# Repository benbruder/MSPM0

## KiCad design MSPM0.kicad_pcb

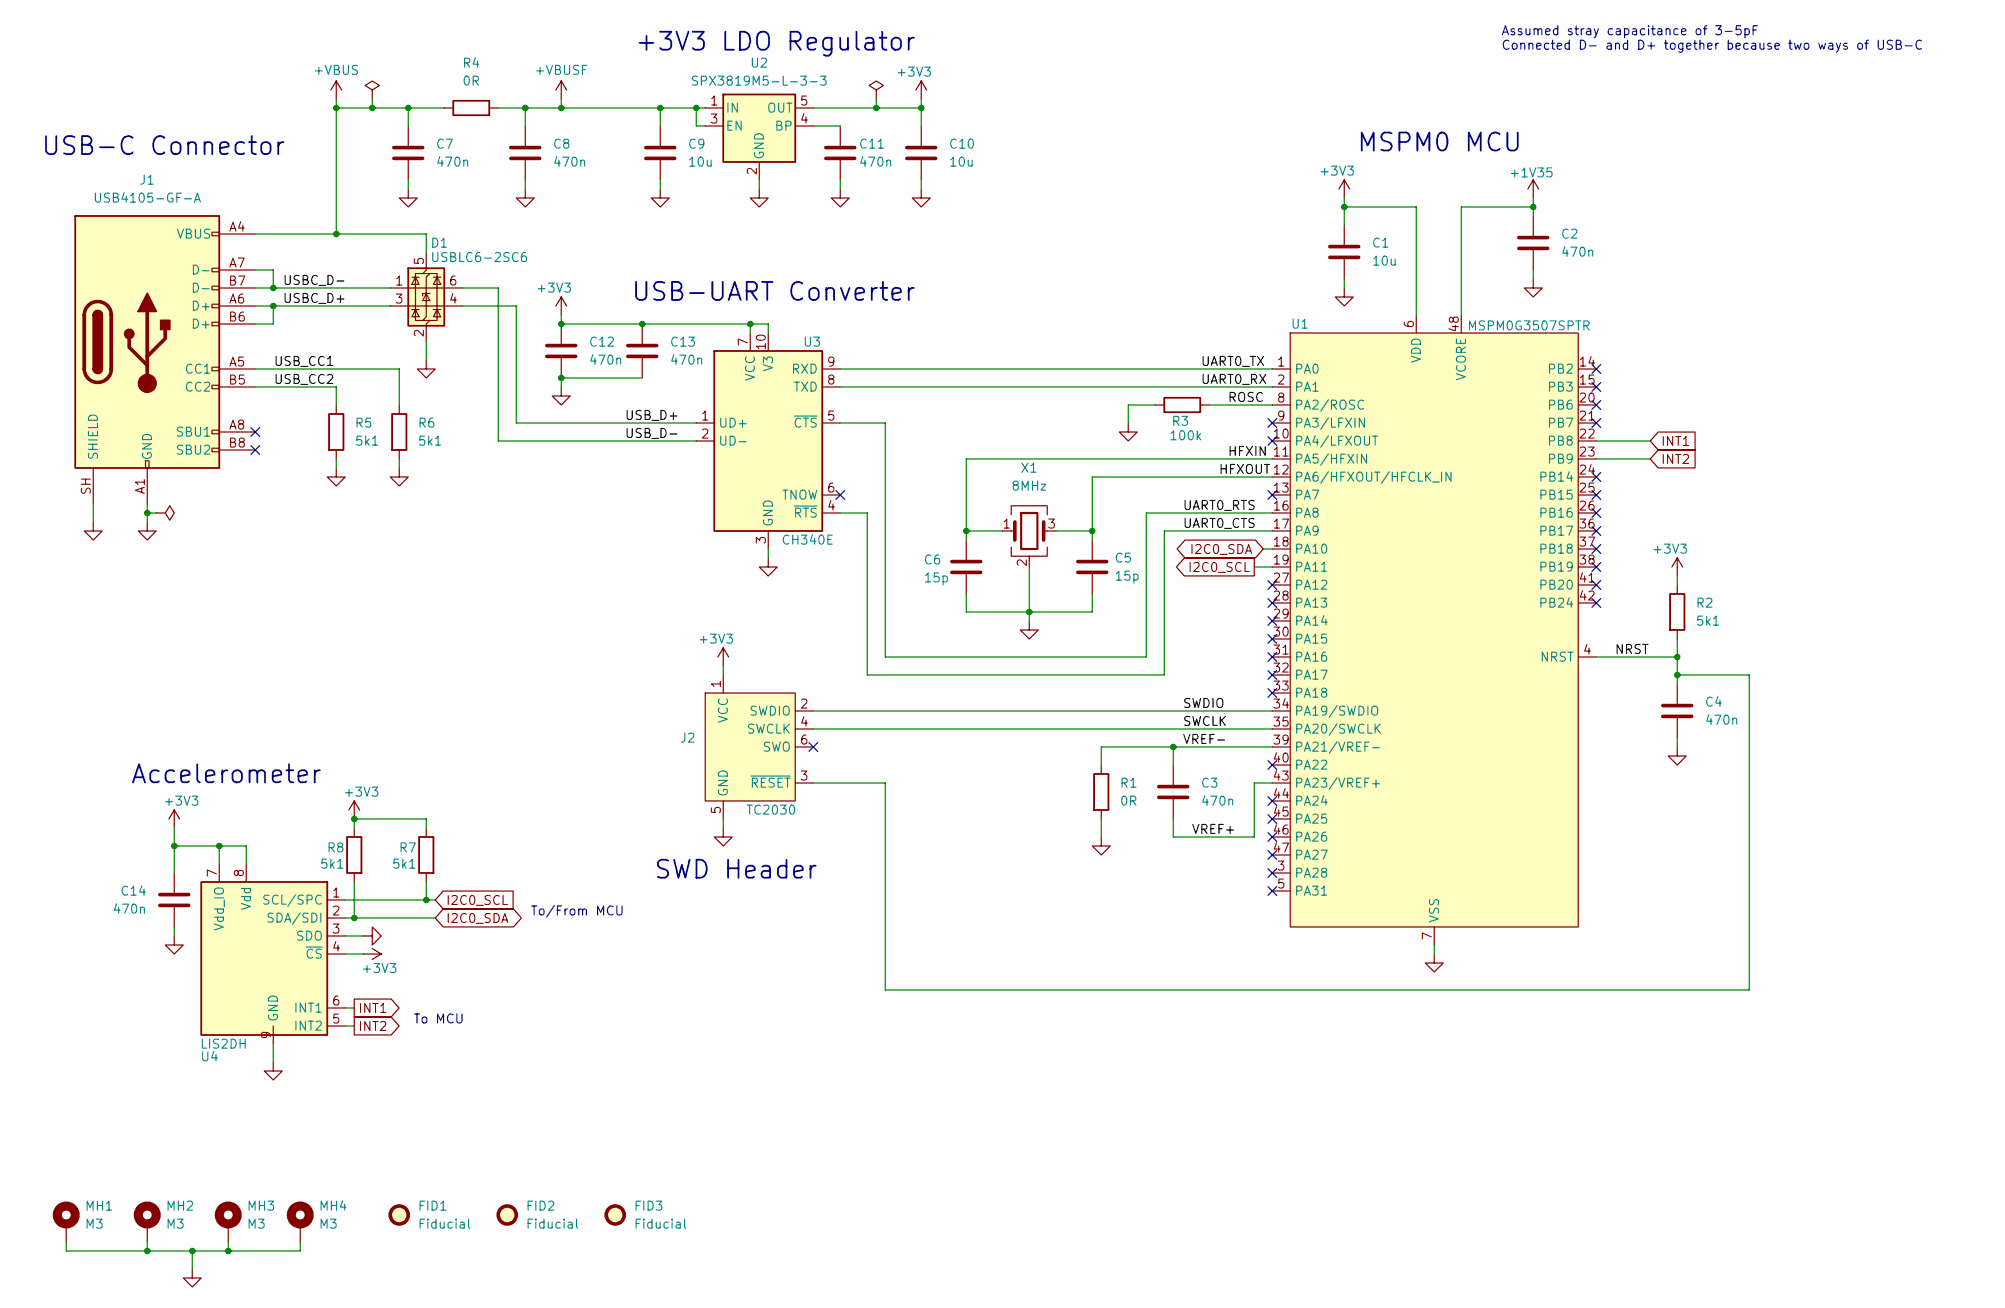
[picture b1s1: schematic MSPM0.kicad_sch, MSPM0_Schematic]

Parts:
C1, C9, C10: 10u; C_0805_2012Metric; Manufacturer Part No. CL21A106KAYNNNE; LCSC C15850
C2, C3, C4, C7, C8, C11, C12, C13, C14: 470n; C_0603_1608Metric; Manufacturer Part No. CL10B474KA8NNNC; LCSC C1623
C5, C6: 15p; C_0603_1608Metric; Manufacturer Part No. CL10C150JB8NNNC
D1: USBLC6-2SC6; SOT-23-6
FID1, FID2, FID3: Fiducial; Fiducial_1mm_Mask2mm
J1: USB4105-GF-A; USB_C_Receptacle_GCT_USB4105-xx-A_16P_TopMnt_Horizontal
J2: TC2030; Tag-Connect_TC2030-IDC-FP_2x03_P1.27mm_Vertical
MH1, MH2, MH3, MH4: M3; MountingHole_3.2mm_M3_Pad_Via
R1, R4: 0R; C_0603_1608Metric
R2, R5, R6, R7, R8: 5k1; C_0603_1608Metric
R3: 100k; C_0603_1608Metric; Manufacturer Part No. RS73F1JTTD1003B
U1: MSPM0G3507SPTR; LQFP-48_7x7mm_P0.5mm; Manufacturer Part No. MSPM0G3507SPTR; LCSC C22362630
U2: SPX3819M5-L-3-3; SOT-23-5
U3: CH340E; MSOP-10_3x3mm_P0.5mm; Manufacturer Part No. CH340E; LCSC C99652
U4: LIS2DH; LGA-14_2x2mm_P0.35mm_LayoutBorder3x4y; Manufacturer Part No. LIS2DHTR; LCSC C155670
X1: 8MHz; Crystal_SMD_3225-4Pin_3.2x2.5mm; Manufacturer Part No. ECS-80-8-33Q-JES-TR

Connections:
+1V35: C2.1, U1.48 (VCORE)
+3V3: C1.1, C10.1, C12.1, C13.1, C14.1, J2.1 (VCC), R2.1, R7.1, R8.1, U1.6 (VDD), U2.5 (OUT), U3.7 (VCC), U3.10 (V3), U4.4 (~CS), U4.7 (Vdd_IO), U4.8 (Vdd)
+VBUS: C7.1, D1.5 (VBUS), J1.A4 (VBUS), J1.A9 (VBUS), J1.B4 (VBUS), J1.B9 (VBUS), R4.1
+VBUSF: C8.1, C9.1, R4.2, U2.1 (IN), U2.3 (EN)
/HFXIN: C6.1, U1.11 (PA5/HFXIN), X1.1
/HFXOUT: C5.1, U1.12 (PA6/HFXOUT/HFCLK_IN), X1.3
/NRST: C4.1, J2.3 (~RESET), R2.2, U1.4 (NRST)
/ROSC: R3.2, U1.8 (PA2/ROSC)
/SWCLK: J2.4 (SWCLK), U1.35 (PA20/SWCLK)
/SWDIO: J2.2 (SWDIO), U1.34 (PA19/SWDIO)
/UART0_CTS: U1.17 (PA9), U3.4 (~RTS)
/UART0_RTS: U1.16 (PA8), U3.5 (~CTS)
/UART0_RX: U1.2 (PA1), U3.8 (TXD)
/UART0_TX: U1.1 (PA0), U3.9 (RXD)
/USBC_D+: D1.3 (I/O2), J1.A6 (D+), J1.B6 (D+)
/USBC_D-: D1.1 (I/O1), J1.A7 (D-), J1.B7 (D-)
/USB_CC1: J1.A5 (CC1), R6.1
/USB_CC2: J1.B5 (CC2), R5.1
/USB_D+: D1.4 (I/O2), U3.1 (UD+)
/USB_D-: D1.6 (I/O1), U3.2 (UD-)
/VREF+: C3.2, U1.43 (PA23/VREF+)
/VREF-: C3.1, R1.1, U1.39 (PA21/VREF-)
GND: C1.2, C2.2, C4.2, C5.2, C6.2, C7.2, C8.2, C9.2, C10.2, C11.2, C12.2, C13.2, C14.2, D1.2 (GND), J1.A1 (GND), J1.A12 (GND), J1.B1 (GND), J1.B12 (GND), J1.SH (SHIELD), J2.5 (GND), MH1.1 (1_1), MH2.1 (1_1), MH3.1 (1_1), MH4.1 (1_1), R1.2, R3.1, R5.2, R6.2, U1.7 (VSS), U2.2 (GND), U3.3 (GND), U4.3 (SDO), U4.9 (GND), U4.10 (GND), U4.11 (GND), U4.12 (GND), U4.13 (GND), U4.14 (GND), X1.2 (G), X1.4 (G)
I2C0_SCL: R7.2, U1.19 (PA11), U4.1 (SCL/SPC)
I2C0_SDA: R8.2, U1.18 (PA10), U4.2 (SDA/SDI)
INT1: U1.22 (PB8), U4.6 (INT1)
INT2: U1.23 (PB9), U4.5 (INT2)
unnamed: C11.1, U2.4 (BP)

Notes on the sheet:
USB-C Connector
SWD Header
MSPM0 MCU
To/From MCU
USB-UART Converter
Assumed stray capacitance of 3-5pF Connected D- and D+ together because two ways of USB-C
Accelerometer
To MCU
+3V3 LDO Regulator

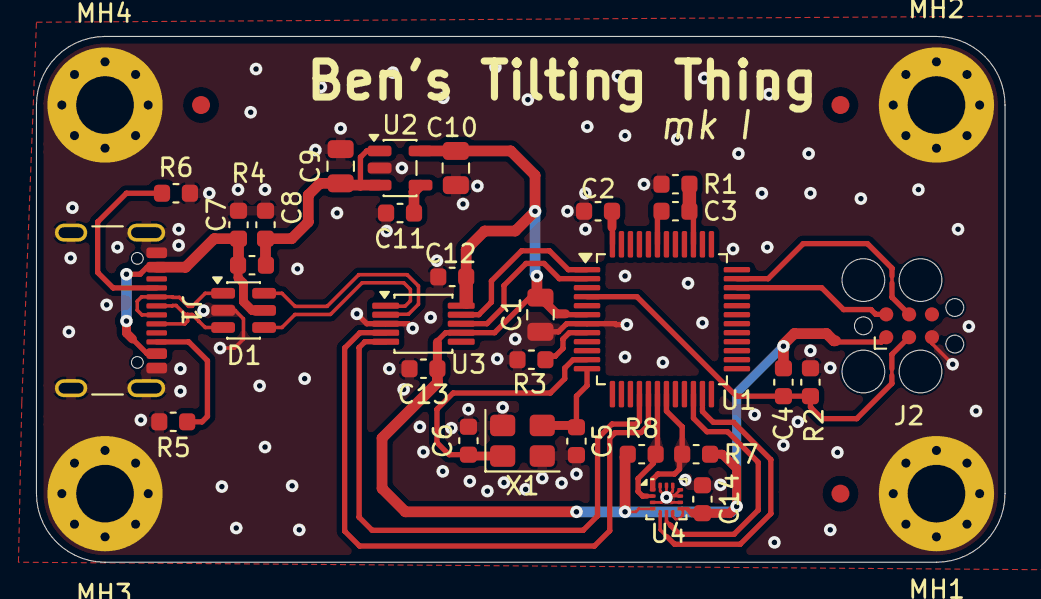
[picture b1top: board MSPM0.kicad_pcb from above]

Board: 2 copper layers, 53.8 x 29.2 mm, 37 parts (0 on the bottom side), 28 nets.

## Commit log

2026-06-07 init
2026-06-08 Finished schematic!!
2026-06-08 Started PCB, fixed schematic footprints Added colors
2026-06-08 Positioned components, made schematic adjustment accordingly Created ground layer
2026-06-08 Completed mk. I
